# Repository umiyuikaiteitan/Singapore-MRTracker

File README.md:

# Singapore-MRTracker

A Rust library and framework that ingests GTFS data for the Singapore
rail network (MRT and LRT). Use it to build interactive live train
maps, destination boards, and LED panels.

(meta note, from yui: this is one of my first large-scale exercises in vibecoding. will keep a cautious eye on it, but it all seems to work for now :3)

## What the project does

- It downloads the official GTFS datasets for trains from LTA
  DataMall.
- It parses GTFS Schedule feeds and builds a linked rail network
  model: lines, stations, interchanges, patterns, and schedules.
- It decodes the GTFS-Realtime feeds for trains: trip updates and
  service alerts.
- It reads the live rail status APIs: train service alerts and
  platform crowd density.
- It merges the static and the live data into render-ready view
  models, and serves a RATIS-style destination board in the browser.
- It publishes the schedule as printed products: a Japanese-style
  station departure timetable (発車時刻表) and a planning-style
  time-distance train diagram (列車ダイヤグラム), as self-contained
  HTML, standalone SVG, and versioned JSON.

## Repository layout

The project is a Cargo workspace. Each library crate is usable on its
own.

| Crate | Purpose |
|-------|---------|
| `crates/mrt-gtfs` | Parse GTFS Schedule feeds. Select the rail subset. Build the network model. Answer schedule queries. |
| `crates/mrt-gtfs-rt` | Decode GTFS-Realtime messages: trip updates, service alerts, vehicle positions. |
| `crates/mrt-datamall` | Talk to the LTA DataMall API: dataset links, downloads, alerts, crowd density. |
| `crates/mrt-live` | Merge the static network with the live data into view models for maps, boards, and panels. |
| `crates/mrt-board-web` | Serve a dot-matrix destination board in the browser (draft). |
| `crates/mrt-board-static` | Generate the board as a static site for GitHub Pages. |
| `crates/mrt-map-web` | Serve the live schematic train map in the browser (proof of concept). |
| `crates/mrt-map-static` | Generate the map as a static site for GitHub Pages, separate from the board. |
| `crates/mrt-publication` | Project the schedule into timetable and train-diagram view models. Pure: no input, no output. |
| `crates/mrt-publication-html` | Render those view models as self-contained HTML and standalone SVG. |
| `crates/mrt-schedule-cli` | The generator: fetch, cache, build, and write timetables and diagrams. |
| `crates/mrt-schedule-site` | Generate a browsable static site of timetables and diagrams for GitHub Pages. |

Other important paths:

| Path | Content |
|------|---------|
| `docs/ARCHITECTURE.md` | The design of the library and the porting notes. |
| `docs/DATA-SOURCES.md` | The DataMall endpoints and their response formats. |
| `docs/DEPLOY-PAGES.md` | How to host the board on GitHub Pages. |
| `docs/SINGAPORE-GTFS-PROFILE.md` | What the LTA train feed carries, and which assumptions are still unverified. |
| `docs/CLI.md` | The `mrt-schedule-cli` reference. |
| `docs/CONFIGURATION.md` | Every configuration option. |
| `docs/KNOWN-LIMITATIONS.md` | What the generator does not do, and why. |
| `docs/LIVE-MAP-POC.md` | The plan for the interactive live train map. |
| `config/singapore.yaml` | A complete, commented configuration. |
| `examples/` | Generated example pages, refreshed by the tests. |
| `scripts/regenerate-gtfs-rt.sh` | The generator for the vendored Protocol Buffer code. |
| `crates/*/examples/` | Small example programs. |

## Data sources

The library reads these LTA DataMall resources:

| Dataset | Endpoint | Format |
|---------|----------|--------|
| GTFS Schedule for trains | `GTFSScheduleTrain` | Link to a GTFS zip archive |
| GTFS-Realtime trip updates | `GTFSRealtimeTrainTripUpdates` | Link to a Protocol Buffer file |
| GTFS-Realtime service alerts | `GTFSRealTimeTrainServiceAlerts` | Link to a Protocol Buffer file |
| Train service alerts (legacy) | `TrainServiceAlerts` | JSON |
| Station crowd density, live | `PCDRealTime` | JSON |
| Station crowd density, forecast | `PCDForecast` | JSON |
| Passenger volume by station | `PV/Train` | Link to a CSV zip archive |

See `docs/DATA-SOURCES.md` for the response formats and examples.

## Quick start

### Requirements

- Rust 1.75 or newer.
- An LTA DataMall account key, for the live data. The static parts of
  the library work without a key.

### Build and test

1. Clone the repository.
2. Run `cargo build --workspace`.
3. Run `cargo test --workspace`.

### Get and set the account key

LTA issues the account key when you register at
<https://datamall.lta.gov.sg>. The key is a secret: keep it out of
source code and commits, and supply it at run time. The `.gitignore`
file excludes `.env` and `*.key` files as a safety net, and the
`AccountKey` type redacts the key in debug output and logs.

Set the key as an environment variable:

```sh
export LTA_DATAMALL_ACCOUNT_KEY=<your key>
```

### Run the examples

Show the live rail status and download the official GTFS Schedule
feed:

```sh
cargo run -p mrt-datamall --example download_gtfs -- data/gtfs_schedule.zip
```

Inspect a feed and list the interchanges:

```sh
cargo run -p mrt-gtfs --example inspect_feed -- data/gtfs_schedule.zip
```

Show a destination board in the terminal:

```sh
cargo run -p mrt-gtfs --example departure_board -- data/gtfs_schedule.zip NS1 20260810 08:00:00
cargo run -p mrt-live --example live_board -- NS1 20260810 08:00:00
```

### Run the board UI

```sh
cargo run -p mrt-board-web
```

Then open <http://127.0.0.1:8600>. The server downloads the official
GTFS Schedule feed at startup, or reads a local copy when you pass a
path:

```sh
cargo run -p mrt-board-web -- data/gtfs_schedule.zip
```

A link opens a station directly through the `station` parameter. It
takes any code of the station, in any spelling, so every code of an
interchange opens the same board.

```text
?station=NS1   ?station=ns1   ?station=ns-1   ?station=EW24
```

The board reads Singapore time (UTC+8) wherever it is opened, and the
status line reports when the page last reached the live status feed.
Its lamp reports the freshness of the DataMall layers behind the last
answer, not the local server: green only when they were freshly
fetched, amber when the board serves aged cache, red when the
upstream is failing or the server stops answering.

To host the board without a server, generate it as a static site.
See `docs/DEPLOY-PAGES.md` for the GitHub Pages workflow:

```sh
cargo run --release -p mrt-board-static -- site data/gtfs_schedule.zip
```

### Run the map UI

The live map has its own server and renderer. Run it independently:

```sh
cargo run -p mrt-map-web
```

Then open <http://127.0.0.1:8601>. The server takes the same feed
argument as the board (`cargo run -p mrt-map-web --
data/gtfs_schedule.zip`), listens where `MRT_MAP_ADDR` says, and draws
the OpenFantasyMap layout named by `MRT_MAP_LAYOUT` (the default is
the miniature fixture layout, `config/layout-mini.geojson` — the prototype fixture only). Without an account key every
train is schedule-only and the page says so.

The deployed map lives at [`/map/`](https://umiyuikaiteitan.github.io/Singapore-MRTracker/map/).
Pages builds it automatically from the real LTA service calendar and the
OSM-reconstructed track shapes. Its browser renderer advances each train
through its complete trip, with a 36-hour schedule and fresh operator delay
updates when available. All locations are labelled as estimates.

The `mrt-map-web` server above remains the schematic prototype. The production
browser map uses `web/live-map`, `mrt-map-schedule`, and
`scripts/build-live-map.mjs`; see [LIVE-MAP.md](docs/LIVE-MAP.md).

### Generate a timetable and a train diagram

A station departure timetable, in the grammar of a Japanese
発車時刻表 — dark hour cells, large minute numerals, small
destination annotations, one panel per platform and direction:

```sh
cargo run -p mrt-schedule-cli -- timetable \
  --feed data/gtfs_schedule.zip \
  --station NS1 \
  --date 2026-08-10 \
  --config config/singapore.yaml \
  --out dist/ns1.html
```

A planning-style train diagram — time across, stations down, one
polyline per train:

```sh
cargo run -p mrt-schedule-cli -- diagram \
  --feed data/gtfs_schedule.zip \
  --line EWL \
  --date 2026-08-10 \
  --from 05:00:00 --until 10:00:00 \
  --config config/singapore.yaml \
  --out dist/ewl.html
```

Both pages are one self-contained file: no external stylesheet,
script, font, or image, a `default-src 'none'` policy, readable
without JavaScript, and printable on A4 and A3. `--format svg` writes
the drawing on its own, and `--format json` writes the versioned view
model for another renderer.

`examples/` holds a generated timetable and diagram, built from the
miniature test feed. See `docs/CLI.md` for the full reference.

### Publish them as a browsable site

`mrt-schedule-site` turns the same generator into a section of the
GitHub Pages site, beside the live board:

```sh
cargo run --release -p mrt-schedule-site -- site/timetables data/gtfs_schedule.zip
```

It writes a hub that lists every line and every station, one
timetable per station and service date, and one diagram per line,
date, and time window. The hub's station list is in the document, so
it works without JavaScript; the search box is an enhancement that
matches a name or any code in any spelling. See `docs/DEPLOY-PAGES.md`
for the workflow and the options.

The generator will not invent data. A headway-based service with
`exact_times=0` becomes `06:30-09:00  every 4 min approximately`
rather than a list of minutes that the feed does not contain; a
platform appears only when the feed names one; and a GTFS `trip_id`
never appears as a train number.

## Library overview

The typical data flow:

```text
DataMall ──> mrt-datamall ──> GTFS zip ──> mrt-gtfs ──> RailNetwork ─┐
                        └──> GTFS-RT pb ──> mrt-gtfs-rt ─────────────┤
                        └──> alerts + crowd JSON ────────────────────┤
                                                                     v
                                                  mrt-live ──> view models
                                                                     v
                                                  mrt-board-web ──> browser

RailNetwork ──> mrt-publication ──> timetable and diagram documents
                                                                     v
                                     mrt-publication-html ──> HTML, SVG
                                                                     v
                                     mrt-schedule-cli ──> files, manifest
```

A minimal program:

```rust,no_run
use mrt_datamall::DataMallClient;
use mrt_gtfs::{GtfsFeed, RailNetwork, ZipSource};
use mrt_live::LiveBoardBuilder;

fn main() {
    // Step 1: download the official GTFS Schedule feed for trains.
    let client = DataMallClient::from_env().unwrap();
    let bytes = client.fetch_gtfs_schedule().unwrap();

    // Step 2: build the rail network model.
    let mut source = ZipSource::from_reader(std::io::Cursor::new(bytes)).unwrap();
    let feed = GtfsFeed::load(&mut source).unwrap();
    let network = RailNetwork::from_feed(&feed).unwrap();

    // Step 3: build a live destination board.
    let alerts = client.train_service_alerts().unwrap();
    let station = network.station_by_code("NS1").unwrap();
    let board = LiveBoardBuilder::new(&network)
        .with_alerts(&alerts)
        .build(station, "20260810".parse().unwrap(), "08:00:00".parse().unwrap(), 1800);

    for row in &board.rows {
        println!("{} {} in {} s", row.line_code, row.destination, row.departs_in_secs);
    }
}
```

All view models serialize to JSON with `serde`, so a web map or an
LED panel driver can consume them directly.

## Design rules

These rules keep the library modular and easy to port to other
languages:

- **Explicit input/output.** The parsers read from the `FeedSource`
  trait. The API client sends requests through the `Transport` trait.
  Tests supply memory sources and mock transports.
- **Plain data models.** The network model uses index identifiers and
  flat structures.
- **Small dependency set.** The core logic uses `csv`, `serde`,
  `prost`, and the standard library. Date and time calculations use
  well-known civil calendar algorithms, implemented in the library.
- **Synchronous code.** Callers wrap the client in the concurrency
  model of their choice.
- **No invented data.** A renderer prints what the feed carries, or an
  explicit configuration override, or nothing. Everything it cannot
  represent becomes a diagnostic rather than a plausible guess.
- **Deterministic artifacts.** The same feed, service date,
  configuration, and generator version produce byte-identical files.
  Generation time lives in the manifest, not in the documents.

## Development

- Format the code: `cargo fmt --all`.
- Lint the code: `cargo clippy --workspace --all-targets`.
- Run the tests: `cargo test --workspace`.

The GitHub Actions workflow in `.github/workflows/ci.yml` runs the
same three commands for every push and pull request. Keep the tests
green. Add a test for every bug fix, so the bug cannot return.

The tests marked `#[ignore]` talk to the live DataMall API. Run them
with your account key when you change the client or the models:

```sh
LTA_DATAMALL_ACCOUNT_KEY=<your key> cargo test --workspace -- --ignored
```

The file `crates/mrt-gtfs-rt/src/transit_realtime.rs` is generated
from `gtfs-realtime.proto`. Run `scripts/regenerate-gtfs-rt.sh` to
update it.

The publication snapshots pin the view models and the drawing. Accept
an intended change with:

```sh
UPDATE_SNAPSHOTS=1 cargo test -p mrt-publication-html
```

`scripts/visual-regression.sh` renders the example pages with a
headless browser and compares them with the baselines in
`examples/baseline/`. It needs Chromium, so it stays out of
`cargo test`.

## Roadmap

The library is the base for these planned applications:

- An interactive live train map: a proof of concept, in
  `crates/mrt-map-web` and `crates/mrt-map-static`, independently hosted
  or as an optional `/map/` section beside the board. See
  [`docs/LIVE-MAP-POC.md`](docs/LIVE-MAP-POC.md) for the plan and what
  each phase shipped: a schematic whole-network map, why the positions
  are derived rather than measured, and how the map says so. One phase
  is still open, and it needs a DataMall account key to verify the feed
  against.
- Station destination boards (draft in `crates/mrt-board-web`).
- Physical LED panel drivers.
- Ports of the core model to other languages.
- A live overlay on the train diagram: scheduled against actual,
  from the GTFS-Realtime trip updates. The interface is written down
  in [`docs/ARCHITECTURE.md`](docs/ARCHITECTURE.md), under "The live
  overlay on the train diagram"; nothing implements it yet.

## Attribution

- Transit data: © Land Transport Authority of Singapore. The data
  comes from LTA DataMall and is subject to the [Singapore Open Data
  Licence](https://datamall.lta.gov.sg/content/datamall/en/SingaporeOpenDataLicence.html).
- `crates/mrt-gtfs-rt/proto/gtfs-realtime.proto`: © The GTFS
  Specifications Authors, Apache License 2.0.
- `crates/mrt-board-web/assets/lta-identity.ttf`: the LTA Identity
  typeface, taken from the MRT-RATIS project for private use.
- This project is not affiliated with the Land Transport Authority.

## Fantasy map editor

The Pages build includes OpenFantasyMap at `/fantasy-map/`, linked from the
board, with a Singapore starting view. Drawing, local projects, GeoJSON
import/export, GTFS-Static rail-network import, selectable OSM tiles/Overpass
views, selectable rail/road following with cached Overpass data, a one-click
Singapore MRT starter, and SVG export work without an application
server or provider key. An optional
`OFM_API_BASE` Actions variable enables a separately hosted matching API.
See [FANTASY-MAP.md](docs/FANTASY-MAP.md) for hosting on `umiyui.dev`, the
snapshot update procedure, and the boundary between static and API features.

The Singapore fantasy-map starter reconstructs missing track shapes from cached
OSM rail topology and removes duplicate directions/short-turns on import.
Coverage and attribution accompany the published starter ZIP.

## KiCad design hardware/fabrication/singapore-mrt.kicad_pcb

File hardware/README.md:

# Singapore MRT physical display build package

This package contains **two separate devices**:

1. A 400 × 256 mm circuit board for **all 146 operating MRT stations**, with one addressable RGB station light per physical station and shared aliases for interchanges. It has 146 populated pixel locations, not a 16-station sample. Each station uses a small WS2812B/SK6812 **RGB module** wired to its carrier socket. The 420 × 298 mm front artwork is an intentional schematic station matrix, grouped by the first MRT line serving each station; it is not a geographic transit map. Line badges identify interchanges. LRT is excluded.
2. An independent Waveshare 7.5-inch V2 800 × 480 black/white e-paper departure board with its own ESP32 and 188 × 136 mm case. It has no LED carrier or LED power supply inside it.

**Prototype status:** routed fabrication data, mechanically dimensioned sources, and automated geometry checks are included. No PCB has been ordered or assembled. `fabrication/validation.json` records what passed and what remains unverified. KiCad's parser/ERC/DRC and a manufacturer's CAM review have not run in this environment; neither electrical performance nor enclosure fit has been measured. Review the CAM and build one first article before ordering a batch.

## What to open

| File | Purpose |
| --- | --- |
| `layouts/singapore-mrt.json` | Stable firmware/publication mapping, indices 0–145, all current and legacy interchange aliases |
| `network-inventory.json` / `NETWORK-COVERAGE.md` | Dated official station coverage and current line paths |
| `fabrication/singapore-mrt.kicad_pcb` | Editable self-contained two-layer PCB source; all footprints embedded |
| `fabrication/gerbers/` | Six Gerbers plus separate plated/non-plated Excellon drills |
| `fabrication/singapore-mrt-gerbers.zip` | Deterministic prototype fabrication upload archive with the same CAM and fabrication notes |
| `docs/assembly-map.svg` | Exact top-view PCB pad, copper, connector, station and index map |
| `docs/led-wiring.svg` | External controller, level shifting and power wiring |
| `docs/epaper-wiring.svg` | Independent e-paper wiring |
| `led-bom.csv` / `epaper-bom.csv` | Separate parts lists |
| `mechanical/led-front-panel-cut.svg` / `led-back-panel-cut.svg` | Exact-scale 3 mm sheet fabrication |
| `mechanical/led-front-artwork.svg` | Full station labels and line colors; print at 100% scale |
| `mechanical/epaper-front-panel-cut.svg` | Separate e-paper bezel |
| `mechanical/enclosures.scad` | Parametric pixel cups, spacers, e-paper shell/front and controller mount |
| `mechanical/*.stl` | Printable meshes exported from that source |

## LED circuit and immutable pinout

The carrier is deliberately a through-hole module design. It routes the 800 kHz data stream through all 146 modules; it does not assume an undocumented bare-LED package. An Adafruit 1612 pixel button is a concrete reference module. Equivalent modules must be **RGB**, 800 kHz GRB WS2812B/SK6812-compatible, and fit the printed cup. RGBW modules use a different wire protocol and do not work with this firmware.

| Connector | Pin | Signal |
| --- | --- | --- |
| P1–P146 | 1 | +5 V for that row |
| P1–P146 | 2 | Module DIN |
| P1–P146 | 3 | GND |
| P1–P146 | 4 | Module DOUT |
| J_DATA_IN | 1 / 2 | Shifted DATA0 / GND |
| J_DATA_OUT | 1 / 2 | DATA146 / GND; optional expansion, no exported power |
| J_PWR1–J_PWR10 | 1 / 2 | Row +5 V / GND; upper/lower in top view |

P1 corresponds to LED index 0. Each complete row has 16 stations; the final row has 2. Even row numbers when counted from zero run left-to-right; odd rows run right-to-left. Consequently the physical P-header pin order reverses on alternate rows. Pin 1 is ringed in the artwork. Always wire by pin number and the module's **printed pad labels**, not by wire color or a photograph. Module power and ground pad duplicates may use either electrically equivalent pair.

Each pixel button is held behind its own 5.5 mm light aperture. Four short insulated wires connect it to its P socket directly behind the aperture. The supplied design therefore makes an actual populated LED circuit-board assembly while retaining replaceable station modules. No assembly-house pick-and-place file is appropriate for this hand-wired version.

The controller connection is `ESP32 GPIO13 → SN74AHCT125 gate 1 → 330 Ω → J_DATA_IN pin 1`. U2 runs at 5 V; the ESP32 stays at 3.3 V logic. Supply U2 pin 14 with 5 V, pin 7 with GND, pin 1 with GND, pin 2 with GPIO13, and pin 3 with the resistor. Fit a 100 nF ceramic at pins 14/7 and a 100 kΩ pulldown at pin 2. Disable unused gates: pins 4/10/13 to +5 V, pins 5/9/12 to GND, leave outputs 6/8/11 unconnected. Keep the shifted data lead short, with an adjacent ground wire.

## Power distribution

Do not feed this entire board through a DevKit USB connector or one pixel header. Worst-case legacy RGB modules can use 60 mA each: **146 × 60 mA = 8.76 A at 5 V** before the controller. Use an enclosed isolated external regulated 5 V supply rated at least 12 A, with a suitable low-voltage distribution block. No mains wiring is part of this build.

Each row has its **own +5 V copper net** and its own paired supply and return wires. Fit one 1.5 A DC-rated fuse close to the distribution block for each of the ten row feeds. Fit a 1000 µF, ≥10 V capacitor across each J_PWR connector near the PCB. The negative lead goes to GND. Use approximately 16 AWG for the short supply trunk and 22 AWG paired row feeds; all terminals and the trunk must be rated for the total load. The 1.5 mm, 2 oz PCB row traces are intended for a maximum 16-pixel row, not the aggregate network load.

Connect **all ten ground returns**, including the final partial row, before powering any row. Grounds share a reference on the PCB, but the inter-row reference trace must not become the substitute return path for missing row wires. Power the ESP32 and AHCT from their own fused branch of the same supply, sharing ground. Use the DevKit's supported input path. Avoid connecting two powered USB/5 V sources simultaneously; development-board power-isolation arrangements vary.

Firmware defaults to a conservative brightness and a 1000 mA **whole-display estimate**. This is intentionally dim. Raise its budget only after measuring total current and the most distant row voltage under the intended pattern. The software limit is not a fuse and does not account precisely for every module revision. At first power-up use current limiting, verify each row's polarity, run a low-brightness single-pixel chase through all 146 indices, then test a moderate static pattern while checking connectors, rail voltage and temperature. A missing or reversed module interrupts all later pixels.

## Fabrication and assembly

Order one 400 × 256 mm, 1.6 mm FR4, two-layer board with 2 oz copper, solder mask both sides and front silkscreen. The CAM uses circular 1.8 mm pads / 1.0 mm finished drills for the pixel/data headers, 2.6 mm pads / 1.3 mm finished drills for power terminals, and six 3.2 mm non-plated mounting holes. Track widths are 0.4 mm data and 1.5 mm power/ground; the checked clearance is 0.25 mm. Large-board pricing and panel availability need a manufacturer quote. Gerber and drill origins match, with +Y up in CAM. The SVG and KiCad views use +Y down. No solder paste layer is needed.

The editable KiCad board and generated CAM share the same copper model. The front CAM uses a simple stroke font for station aliases and socket numbers; it is intentionally independent of installed system fonts. Open all layers and drills together in a CAM viewer before fabrication, check the 400 × 256 mm outline and hole registration, and have the board shop review plating and clearance requirements. KiCad source regeneration overwrites manual edits; change `scripts/generate.py` if you want reproducible routing changes.

Cut the LED front/back SVGs from 3 mm sheet at 100% scale. Red paths are cuts; artwork is a separate print, not a cut layer. No laser kerf compensation is embedded: the shop should apply its measured kerf outward for external edges and inward for holes. Check a 100 mm printed ruler against the machine's scale before cutting. Panel outline is 420 × 298 mm. Six 34 mm spacers plus M3×45 bolts and nuts make a 40 mm total-depth open-sided sandwich. Six 12 mm PCB standoffs mount the carrier to the rear sheet; PCB origin is 10 mm right and 24 mm down from the panel origin. The aligned six PCB holes are present in the back sheet.

Print cups and spacers in PETG at 0.2 mm layers; trial-fit **one** cup to the purchased pixel module and aperture first. Print cup copies as needed, attach their flat optical faces to the back of the front panel with foam tape, and use a translucent diffuser over each aperture. Insert the pixels from the rear; retain them without stressing their solder joints. Route short pigtails to the corresponding sockets and provide strain relief for the main cable through the 12 mm rear opening. The modular printed parts fit a normal desktop printer; neither a 420 mm printer nor a combined e-paper enclosure is required. The open-sided format permits inspection and cooling; add an independently designed side guard if the final installation requires one.

The e-paper case uses a separate 188 × 136 × 28 mm printed shell and 3 mm front bezel. Its 164.2 × 99 mm opening is slightly larger than the panel's specified 163.2 × 97.92 mm active area. The actual glass outline is 170.2 × 111.2 mm. Align the active image to the opening before applying low-pressure foam tape to the glass perimeter; the shell deliberately does not assume symmetric active-area margins or a particular HAT mounting-hole pattern. Keep the FPC unstressed. Use the universal perforated mount, insulating tape and cable ties for the DevKit and matching driver HAT. The exposed glass and cable still require a physical fit trial.

## E-paper electrical contract

Use the **matching driver HAT/module**, not the panel's bare 24-pin FPC. This device uses a separate ESP32-WROOM-32 DevKit; ESP32-WROVER boards may reserve GPIO16/17 for PSRAM. Power the DevKit through USB and the HAT from its 3.3 V rail so its SPI interface shares the ESP32 logic level. Confirm the purchased HAT revision supports this supply and its manual's reset/timing settings.

| HAT signal | ESP32 |
| --- | --- |
| VCC / GND | 3V3 / GND |
| DIN / CLK | GPIO23 / GPIO18 |
| CS / DC | GPIO5 / GPIO17 |
| RST / BUSY | GPIO16 / GPIO4 |

No MISO connection is used. Never connect a 5 V signal to an ESP32 input. GPIO5 is a strapping pin; the specified driver should not force its level at reset. Use short leads and check a cold boot with the actual module. The intended firmware driver is GxEPD2_750_T7 for the V2 black/white 800 × 480 panel; similarly named 640 × 384, three-color and other controller revisions are not interchangeable.

## Reproduce and validate

```sh
python3 hardware/scripts/generate.py
python3 hardware/scripts/validate.py
openscad -D 'part="led_parts"' -o hardware/mechanical/led-spacers-and-cups.stl hardware/mechanical/enclosures.scad
openscad -D 'part="epaper_shell"' -o hardware/mechanical/epaper-shell.stl hardware/mechanical/enclosures.scad
openscad -D 'part="epaper_front"' -o hardware/mechanical/epaper-front.stl hardware/mechanical/enclosures.scad
openscad -D 'part="epaper_mount"' -o hardware/mechanical/epaper-electronics-mount.stl hardware/mechanical/enclosures.scad
python3 hardware/scripts/validate_mechanical.py
```

Optional PNG previews use `node hardware/scripts/render-previews.js` with the `sharp` package installed. The SVG sources are the exact-scale originals. `fabrication/mechanical-validation.json` checks the 146 aperture positions, six PCB mounting holes, front/back registration, e-paper boss registration, closed STL edges and the exported enclosure envelopes. Printer shrinkage, laser kerf and purchased-part fit remain physical checks.

The Python validator independently checks copper clearance, annular rings, edge/hole spacing, electrical connectivity of every routed net, per-pixel pinout, station/alias coverage, contiguous indices and exact generated CAM parity. It does not implement full KiCad DRC, electrical rules checking, impedance analysis or thermal analysis. Its explicit limitations are retained in the report. E-paper SPI timings, power sequencing and display refresh intervals require the purchased module and a bench test.

The default matrix can be replaced by a more geographic schematic in a future board revision, but the topology data is already present in `network-inventory.json`. Preserve LED indices or deliberately version `layout_id` when moving station assignments. Do not relabel the physical artwork while leaving an old mapping on the device.

## Primary references

- [Adafruit NeoPixel Mini Button 1612](https://www.adafruit.com/product/1612): reference RGB module, dimensions, protocol and conservative current requirement. Availability and module revisions vary.
- [Texas Instruments SN74AHCT125](https://www.ti.com/product/SN74AHCT125) and [datasheet](https://www.ti.com/lit/ds/symlink/sn74ahct125.pdf): 5 V TTL-compatible input buffer and pin connections.
- [Waveshare 7.5-inch V2 specification](https://files.waveshare.com/upload/6/60/7.5inch_e-Paper_V2_Specification.pdf): 800 × 480 resolution, glass/active-area dimensions and panel interface. The matching HAT adds the power/driver circuitry; its revision-specific instructions still apply.
- [LTA Thomson–East Coast Line](https://www.lta.gov.sg/content/ltagov/en/upcoming_projects/rail_expansion/thomson_east_coast_line.html) plus the dated full-network sources in `NETWORK-COVERAGE.md` establish station coverage.

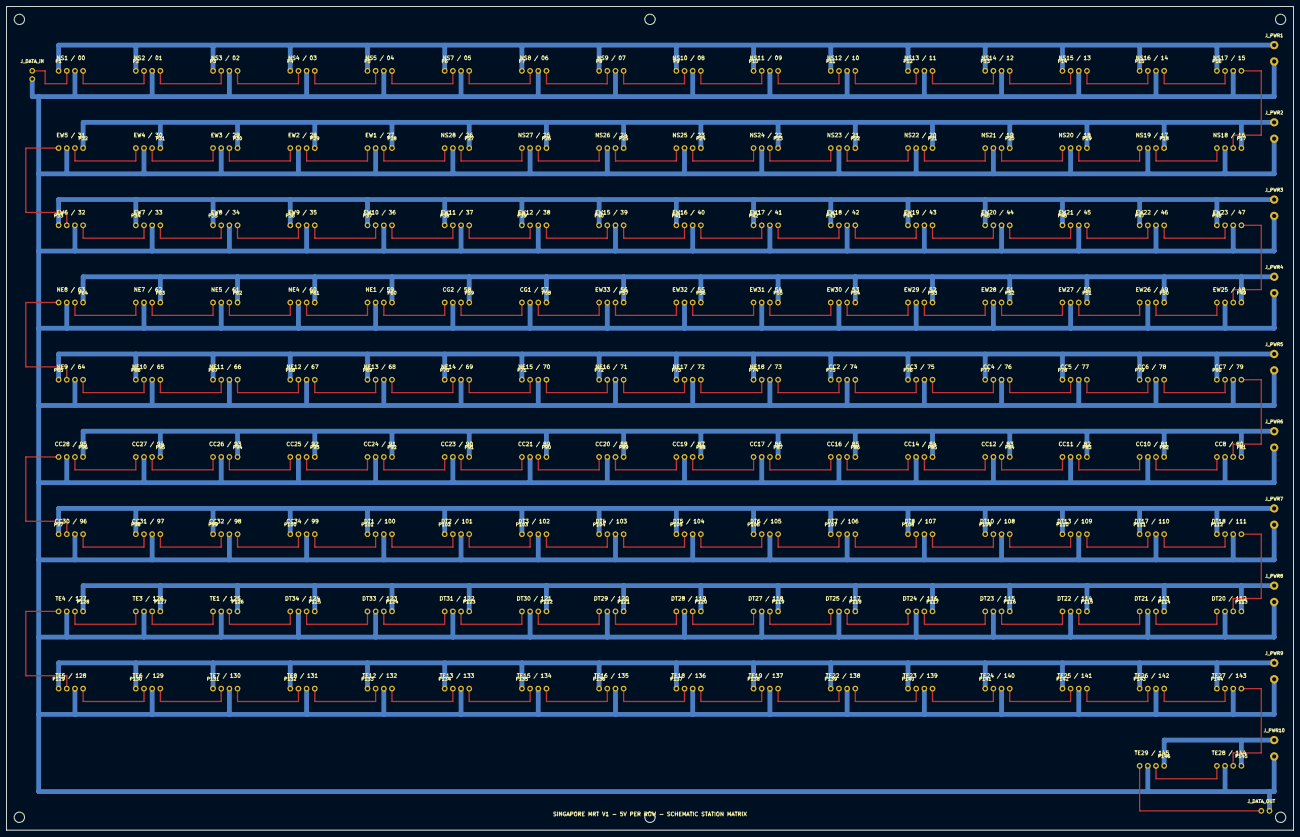
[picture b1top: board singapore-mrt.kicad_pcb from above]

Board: 2 copper layers, 400.0 x 256.0 mm, 164 parts (0 on the bottom side), 158 nets.

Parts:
H1, H2, H3, H4, H5, H6: MountingHole_3.2
J_DATA_IN: Wired_Header_2
J_DATA_OUT: Wired_Header_2
J_PWR1, J_PWR2, J_PWR3, J_PWR4, J_PWR5, J_PWR6, J_PWR7, J_PWR8, J_PWR9, J_PWR10: Wired_Header_2
P1, P2, P3, P4, P5, P6, P7, P8, P9, P10, P11, P12, P13, P14, P15, P16, P17, P18, P19, P20, P21, P22, P23, P24, P25, P26, P27, P28, P29, P30, P31, P32, P33, P34, P35, P36, P37, P38, P39, P40, P41, P42, P43, P44, P45, P46, P47, P48, P49, P50, P51, P52, P53, P54, P55, P56, P57, P58, P59, P60, P61, P62, P63, P64, P65, P66, P67, P68, P69, P70, P71, P72, P73, P74, P75, P76, P77, P78, P79, P80, P81, P82, P83, P84, P85, P86, P87, P88, P89, P90, P91, P92, P93, P94, P95, P96, P97, P98, P99, P100, P101, P102, P103, P104, P105, P106, P107, P108, P109, P110, P111, P112, P113, P114, P115, P116, P117, P118, P119, P120, P121, P122, P123, P124, P125, P126, P127, P128, P129, P130, P131, P132, P133, P134, P135, P136, P137, P138, P139, P140, P141, P142, P143, P144, P145, P146: Wired_Header_4

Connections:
+5V_ROW1: J_PWR1.1, P1.1, P2.1, P3.1, P4.1, P5.1, P6.1, P7.1, P8.1, P9.1, P10.1, P11.1, P12.1, P13.1, P14.1, P15.1, P16.1
+5V_ROW2: J_PWR2.1, P17.1, P18.1, P19.1, P20.1, P21.1, P22.1, P23.1, P24.1, P25.1, P26.1, P27.1, P28.1, P29.1, P30.1, P31.1, P32.1
+5V_ROW3: J_PWR3.1, P33.1, P34.1, P35.1, P36.1, P37.1, P38.1, P39.1, P40.1, P41.1, P42.1, P43.1, P44.1, P45.1, P46.1, P47.1, P48.1
+5V_ROW4: J_PWR4.1, P49.1, P50.1, P51.1, P52.1, P53.1, P54.1, P55.1, P56.1, P57.1, P58.1, P59.1, P60.1, P61.1, P62.1, P63.1, P64.1
+5V_ROW5: J_PWR5.1, P65.1, P66.1, P67.1, P68.1, P69.1, P70.1, P71.1, P72.1, P73.1, P74.1, P75.1, P76.1, P77.1, P78.1, P79.1, P80.1
+5V_ROW6: J_PWR6.1, P81.1, P82.1, P83.1, P84.1, P85.1, P86.1, P87.1, P88.1, P89.1, P90.1, P91.1, P92.1, P93.1, P94.1, P95.1, P96.1
+5V_ROW7: J_PWR7.1, P97.1, P98.1, P99.1, P100.1, P101.1, P102.1, P103.1, P104.1, P105.1, P106.1, P107.1, P108.1, P109.1, P110.1, P111.1, P112.1
+5V_ROW8: J_PWR8.1, P113.1, P114.1, P115.1, P116.1, P117.1, P118.1, P119.1, P120.1, P121.1, P122.1, P123.1, P124.1, P125.1, P126.1, P127.1, P128.1
+5V_ROW9: J_PWR9.1, P129.1, P130.1, P131.1, P132.1, P133.1, P134.1, P135.1, P136.1, P137.1, P138.1, P139.1, P140.1, P141.1, P142.1, P143.1, P144.1
+5V_ROW10: J_PWR10.1, P145.1, P146.1
DATA0: J_DATA_IN.1, P1.2
DATA1: P1.4, P2.2
DATA2: P2.4, P3.2
DATA3: P3.4, P4.2
DATA4: P4.4, P5.2
DATA5: P5.4, P6.2
DATA6: P6.4, P7.2
DATA7: P7.4, P8.2
DATA8: P8.4, P9.2
DATA9: P9.4, P10.2
DATA10: P10.4, P11.2
DATA11: P11.4, P12.2
DATA12: P12.4, P13.2
DATA13: P13.4, P14.2
DATA14: P14.4, P15.2
DATA15: P15.4, P16.2
DATA16: P16.4, P17.2
DATA17: P17.4, P18.2
DATA18: P18.4, P19.2
DATA19: P19.4, P20.2
DATA20: P20.4, P21.2
DATA21: P21.4, P22.2
DATA22: P22.4, P23.2
DATA23: P23.4, P24.2
DATA24: P24.4, P25.2
DATA25: P25.4, P26.2
DATA26: P26.4, P27.2
DATA27: P27.4, P28.2
DATA28: P28.4, P29.2
DATA29: P29.4, P30.2
DATA30: P30.4, P31.2
DATA31: P31.4, P32.2
DATA32: P32.4, P33.2
DATA33: P33.4, P34.2
DATA34: P34.4, P35.2
DATA35: P35.4, P36.2
DATA36: P36.4, P37.2
DATA37: P37.4, P38.2
DATA38: P38.4, P39.2
DATA39: P39.4, P40.2
DATA40: P40.4, P41.2
DATA41: P41.4, P42.2
DATA42: P42.4, P43.2
DATA43: P43.4, P44.2
DATA44: P44.4, P45.2
DATA45: P45.4, P46.2
DATA46: P46.4, P47.2
DATA47: P47.4, P48.2
DATA48: P48.4, P49.2
DATA49: P49.4, P50.2
DATA50: P50.4, P51.2
DATA51: P51.4, P52.2
DATA52: P52.4, P53.2
DATA53: P53.4, P54.2
DATA54: P54.4, P55.2
DATA55: P55.4, P56.2
DATA56: P56.4, P57.2
DATA57: P57.4, P58.2
DATA58: P58.4, P59.2
DATA59: P59.4, P60.2
DATA60: P60.4, P61.2
DATA61: P61.4, P62.2
DATA62: P62.4, P63.2
DATA63: P63.4, P64.2
DATA64: P64.4, P65.2
DATA65: P65.4, P66.2
DATA66: P66.4, P67.2
DATA67: P67.4, P68.2
DATA68: P68.4, P69.2
DATA69: P69.4, P70.2
DATA70: P70.4, P71.2
DATA71: P71.4, P72.2
DATA72: P72.4, P73.2
DATA73: P73.4, P74.2
DATA74: P74.4, P75.2
DATA75: P75.4, P76.2
DATA76: P76.4, P77.2
DATA77: P77.4, P78.2
DATA78: P78.4, P79.2
DATA79: P79.4, P80.2
DATA80: P80.4, P81.2
DATA81: P81.4, P82.2
DATA82: P82.4, P83.2
DATA83: P83.4, P84.2
DATA84: P84.4, P85.2
DATA85: P85.4, P86.2
DATA86: P86.4, P87.2
DATA87: P87.4, P88.2
DATA88: P88.4, P89.2
DATA89: P89.4, P90.2
DATA90: P90.4, P91.2
DATA91: P91.4, P92.2
DATA92: P92.4, P93.2
DATA93: P93.4, P94.2
DATA94: P94.4, P95.2
DATA95: P95.4, P96.2
DATA96: P96.4, P97.2
DATA97: P97.4, P98.2
DATA98: P98.4, P99.2
DATA99: P99.4, P100.2
DATA100: P100.4, P101.2
DATA101: P101.4, P102.2
DATA102: P102.4, P103.2
DATA103: P103.4, P104.2
DATA104: P104.4, P105.2
DATA105: P105.4, P106.2
DATA106: P106.4, P107.2
DATA107: P107.4, P108.2
DATA108: P108.4, P109.2
DATA109: P109.4, P110.2
DATA110: P110.4, P111.2
DATA111: P111.4, P112.2
DATA112: P112.4, P113.2
DATA113: P113.4, P114.2
DATA114: P114.4, P115.2
DATA115: P115.4, P116.2
DATA116: P116.4, P117.2
DATA117: P117.4, P118.2
DATA118: P118.4, P119.2
DATA119: P119.4, P120.2
DATA120: P120.4, P121.2
DATA121: P121.4, P122.2
DATA122: P122.4, P123.2
DATA123: P123.4, P124.2
DATA124: P124.4, P125.2
DATA125: P125.4, P126.2
DATA126: P126.4, P127.2
DATA127: P127.4, P128.2
DATA128: P128.4, P129.2
DATA129: P129.4, P130.2
DATA130: P130.4, P131.2
DATA131: P131.4, P132.2
DATA132: P132.4, P133.2
DATA133: P133.4, P134.2
DATA134: P134.4, P135.2
DATA135: P135.4, P136.2
DATA136: P136.4, P137.2
DATA137: P137.4, P138.2
DATA138: P138.4, P139.2
DATA139: P139.4, P140.2
DATA140: P140.4, P141.2
DATA141: P141.4, P142.2
DATA142: P142.4, P143.2
DATA143: P143.4, P144.2
DATA144: P144.4, P145.2
DATA145: P145.4, P146.2
DATA146: J_DATA_OUT.1, P146.4
GND: J_DATA_IN.2, J_DATA_OUT.2, J_PWR1.2, J_PWR2.2, J_PWR3.2, J_PWR4.2, J_PWR5.2, J_PWR6.2, J_PWR7.2, J_PWR8.2, J_PWR9.2, J_PWR10.2, P1.3, P2.3, P3.3, P4.3, P5.3, P6.3, P7.3, P8.3, P9.3, P10.3, P11.3, P12.3, P13.3, P14.3, P15.3, P16.3, P17.3, P18.3, P19.3, P20.3, P21.3, P22.3, P23.3, P24.3, P25.3, P26.3, P27.3, P28.3, P29.3, P30.3, P31.3, P32.3, P33.3, P34.3, P35.3, P36.3, P37.3, P38.3, P39.3, P40.3, P41.3, P42.3, P43.3, P44.3, P45.3, P46.3, P47.3, P48.3, P49.3, P50.3, P51.3, P52.3, P53.3, P54.3, P55.3, P56.3, P57.3, P58.3, P59.3, P60.3, P61.3, P62.3, P63.3, P64.3, P65.3, P66.3, P67.3, P68.3, P69.3, P70.3, P71.3, P72.3, P73.3, P74.3, P75.3, P76.3, P77.3, P78.3, P79.3, P80.3, P81.3, P82.3, P83.3, P84.3, P85.3, P86.3, P87.3, P88.3, P89.3, P90.3, P91.3, P92.3, P93.3, P94.3, P95.3, P96.3, P97.3, P98.3, P99.3, P100.3, P101.3, P102.3, P103.3, P104.3, P105.3, P106.3, P107.3, P108.3, P109.3, P110.3, P111.3, P112.3, P113.3, P114.3, P115.3, P116.3, P117.3, P118.3, P119.3, P120.3, P121.3, P122.3, P123.3, P124.3, P125.3, P126.3, P127.3, P128.3, P129.3, P130.3, P131.3, P132.3, P133.3, P134.3, P135.3, P136.3, P137.3, P138.3, P139.3, P140.3, P141.3, P142.3, P143.3, P144.3, P145.3, P146.3
